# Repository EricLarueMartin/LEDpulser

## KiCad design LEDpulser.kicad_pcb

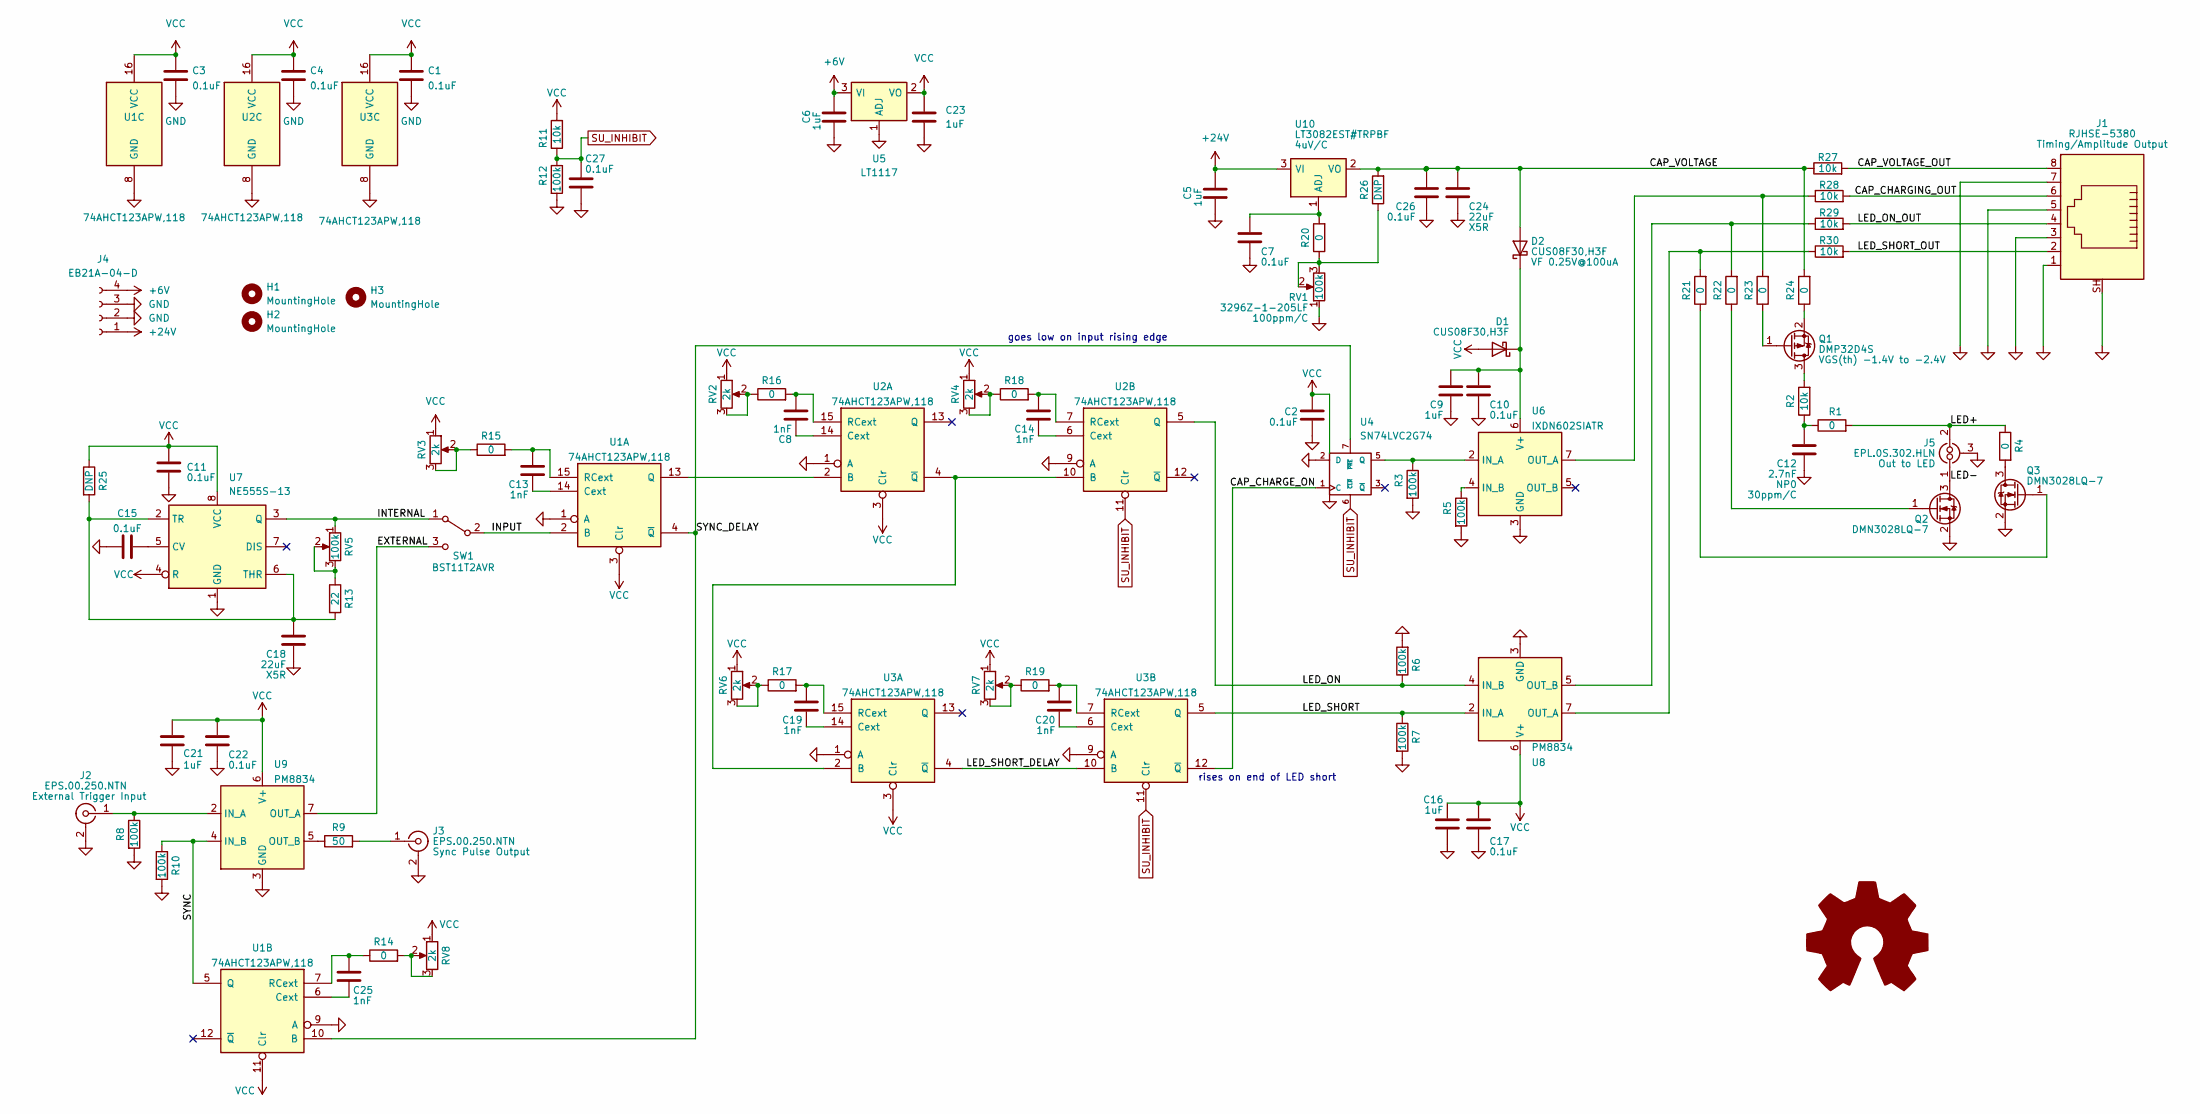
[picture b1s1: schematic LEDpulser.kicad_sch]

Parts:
C1, C2, C3, C4, C10, C11, C15, C17, C22, C26, C27: 0.1uF; C_0603_1608Metric
C5, C6, C9, C16, C21, C23: 1uF; C_0603_1608Metric
C7: 0.1uF; C_0805_2012Metric
C8, C13, C14, C19, C20, C25: 1nF; C_0603_1608Metric
C12: 2.7nF; C_0603_1608Metric
C18, C24: 22uF; C_0805_2012Metric
D1, D2: CUS08F30,H3F; D_SOD-323
H1, H2, H3: MountingHole; MountingHole_3.2mm_M3
J1: RJHSE-5380; RJ45_Amphenol_RJHSE5380
J2, J3: EPS.00.250.NTN; SMA_Amphenol_132203-12_Horizontal
J4: EB21A-04-D; TerminalBlock_Phoenix_MKDS-1,5-4-5.08_1x04_P5.08mm_Horizont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
J5: EPL.0S.302.HLN; FanPinHeader_1x03_P2.54mm_Vertical
Q1: DMP32D4S; SOT-23
Q2, Q3: DMN3028LQ-7; SOT-23
R1, R4, R14, R15, R16, R17, R18, R19, R20, R21, R22, R23, R24: 0; R_0603_1608Metric
R2, R11, R27, R28, R29, R30: 10k; R_0603_1608Metric
R3, R5, R6, R7, R8, R10, R12: 100k; R_0603_1608Metric
R9: 50; R_1206_3216Metric
R13: 22; R_0603_1608Metric
R25, R26: DNP; R_0603_1608Metric
RV1: 100k; Potentiometer_Bourns_3266X_Horizontal; Part# 3296Z-1-205LF
RV2: 2k; Potentiometer_Bourns_3266W_Vertical; Part# 3262X-1-501LF
RV3: 2k; Potentiometer_Bourns_3266X_Horizontal; Part# 3262X-1-501LF
RV4, RV6, RV7: 2k; Potentiometer_Bourns_3266W_Vertical; Part# 3296Y-1-202LF
RV5: 100k; Potentiometer_Bourns_3266X_Horizontal; Part# 3296Z-1-104LF
RV8: 2k; Potentiometer_Bourns_3266X_Horizontal; Part# 3262X-1-202LF
SW1: BST11T2AVR; SW_Lever_1P2T_NKK_GW12LxH
U1, U2, U3: 74AHCT123APW,118; TSSOP-16_4.4x5mm_P0.65mm
U4: SN74LVC2G74; SSOP-8_2.95x2.8mm_P0.65mm
U5: LT1117; SOT-223-3_TabPin2
U6: IXDN602SIATR; SO-8_3.9x4.9mm_P1.27mm
U7: NE555S-13; SO-8_3.9x4.9mm_P1.27mm
U8, U9: PM8834; SO-8_3.9x4.9mm_P1.27mm
U10: LT3082EST#TRPBF; SOT-223-3_TabPin2

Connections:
+6V: C6.1, J4.4, U5.3 (VI)
+24V: C5.1, J4.1, U10.3 (VI)
/CAP_CHARGE_ON: U3.12 (~Q), U4.1 (C)
/CAP_CHARGING_OUT: J1.6, R28.2
/CAP_VOLTAGE: C24.1, C26.1, D2.2 (A), R24.2, R26.2, R27.1, U10.2 (VO)
/CAP_VOLTAGE_OUT: J1.8, R27.2
/EXTERNAL: SW1.3 (C), U9.7 (OUT_A)
/INPUT: SW1.2 (B), U1.2 (B)
/INTERNAL: RV5.1, SW1.1 (A), U7.3 (Q)
/LED+: J5.2 (In2), R1.2, R4.1
/LED-: J5.1 (In1), Q2.3 (D)
/LED_ON: R6.1, U2.5 (Q), U8.4 (IN_B)
/LED_ON_OUT: J1.4, R29.2
/LED_SHORT: R7.1, U3.5 (Q), U8.2 (IN_A)
/LED_SHORT_DELAY: U3.4 (~Q), U3.10 (B)
/LED_SHORT_OUT: J1.2, R30.2
/SYNC: R10.1, U1.5 (Q), U9.4 (IN_B)
/SYNC_DELAY: U1.4 (~Q), U1.10 (B), U4.7 (~PRE)
GND: C1.2, C2.2, C3.2, C4.2, C5.2, C6.2, C7.2, C9.2, C10.2, C11.2, C12.2, C15.2, C16.2, C17.2, C18.2, C21.2, C22.2, C23.2, C24.2, C26.2, C27.2, J1.1, J1.3, J1.5, J1.7, J1.SH, J2.2 (Ext), J3.2 (Ext), J4.2, J4.3, J5.3 (Ext), Q2.2 (S), Q3.2 (S), R3.2, R5.2, R6.2, R7.2, R8.2, R10.2, R12.2, RV1.1, U1.1 (A), U1.8 (GND), U1.9 (A), U2.1 (A), U2.8 (GND), U2.9 (A), U3.1 (A), U3.8 (GND), U3.9 (A), U4.2 (D), U4.4 (GND), U5.1 (ADJ), U6.3 (GND), U7.1 (GND), U8.3 (GND), U9.3 (GND)
unnamed: C7.1, R20.2, U10.1 (ADJ)
unnamed: C8.1, U2.14 (Cext)
unnamed: C8.2, R16.2, U2.15 (RCext)
unnamed: C9.1, C10.1, D1.1 (K), D2.1 (K), U6.6 (V+)
unnamed: C12.1, R1.1, R2.1
unnamed: C13.1, R15.2, U1.15 (RCext)
unnamed: C13.2, U1.14 (Cext)
unnamed: C14.1, R18.2, U2.7 (RCext)
unnamed: C14.2, U2.6 (Cext)
unnamed: C15.1, U7.5 (CV)
unnamed: C18.1, R13.2, R25.2, U7.2 (TR), U7.6 (THR)
unnamed: C19.1, R17.2, U3.15 (RCext)
unnamed: C19.2, U3.14 (Cext)
unnamed: C20.1, R19.2, U3.7 (RCext)
unnamed: C20.2, U3.6 (Cext)
unnamed: C25.1, R14.1, U1.7 (RCext)
unnamed: C25.2, U1.6 (Cext)
unnamed: J2.1 (In), R8.1, U9.2 (IN_A)
unnamed: J3.1 (In), R9.2
unnamed: Q1.1 (G), R23.1
unnamed: Q1.2 (S), R24.1
unnamed: Q1.3 (D), R2.2
unnamed: Q2.1 (G), R22.1
unnamed: Q3.1 (G), R21.1
unnamed: Q3.3 (D), R4.2
unnamed: R3.1, U4.5 (Q), U6.2 (IN_A)
unnamed: R5.1, U6.4 (IN_B)
unnamed: R9.1, U9.5 (OUT_B)
unnamed: R13.1, RV5.2, RV5.3
unnamed: R14.2, RV8.2, RV8.3
unnamed: R15.1, RV3.2, RV3.3
unnamed: R16.1, RV2.2, RV2.3
unnamed: R17.1, RV6.2, RV6.3
unnamed: R18.1, RV4.2, RV4.3
unnamed: R19.1, RV7.2, RV7.3
unnamed: R20.1, R26.1, RV1.2, RV1.3
unnamed: R21.2, R30.1, U8.7 (OUT_A)
unnamed: R22.2, R29.1, U8.5 (OUT_B)
unnamed: R23.2, R28.1, U6.7 (OUT_A)
unnamed: U1.13 (Q), U2.2 (B)
unnamed: U2.4 (~Q), U2.10 (B), U3.2 (B)
SU_INHIBIT: C27.1, R11.1, R12.1, U2.11 (Clr), U3.11 (Clr), U4.6 (~CLR)
VCC: C1.1, C2.1, C3.1, C4.1, C11.1, C16.1, C17.1, C21.1, C22.1, C23.1, D1.2 (A), R11.2, R25.1, RV2.1, RV3.1, RV4.1, RV6.1, RV7.1, RV8.1, U1.3 (Clr), U1.11 (Clr), U1.16 (VCC), U2.3 (Clr), U2.16 (VCC), U3.3 (Clr), U3.16 (VCC), U4.8 (VCC), U5.2 (VO), U7.4 (R), U7.8 (VCC), U8.6 (V+), U9.6 (V+)

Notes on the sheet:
rises on end of LED short
goes low on input rising edge

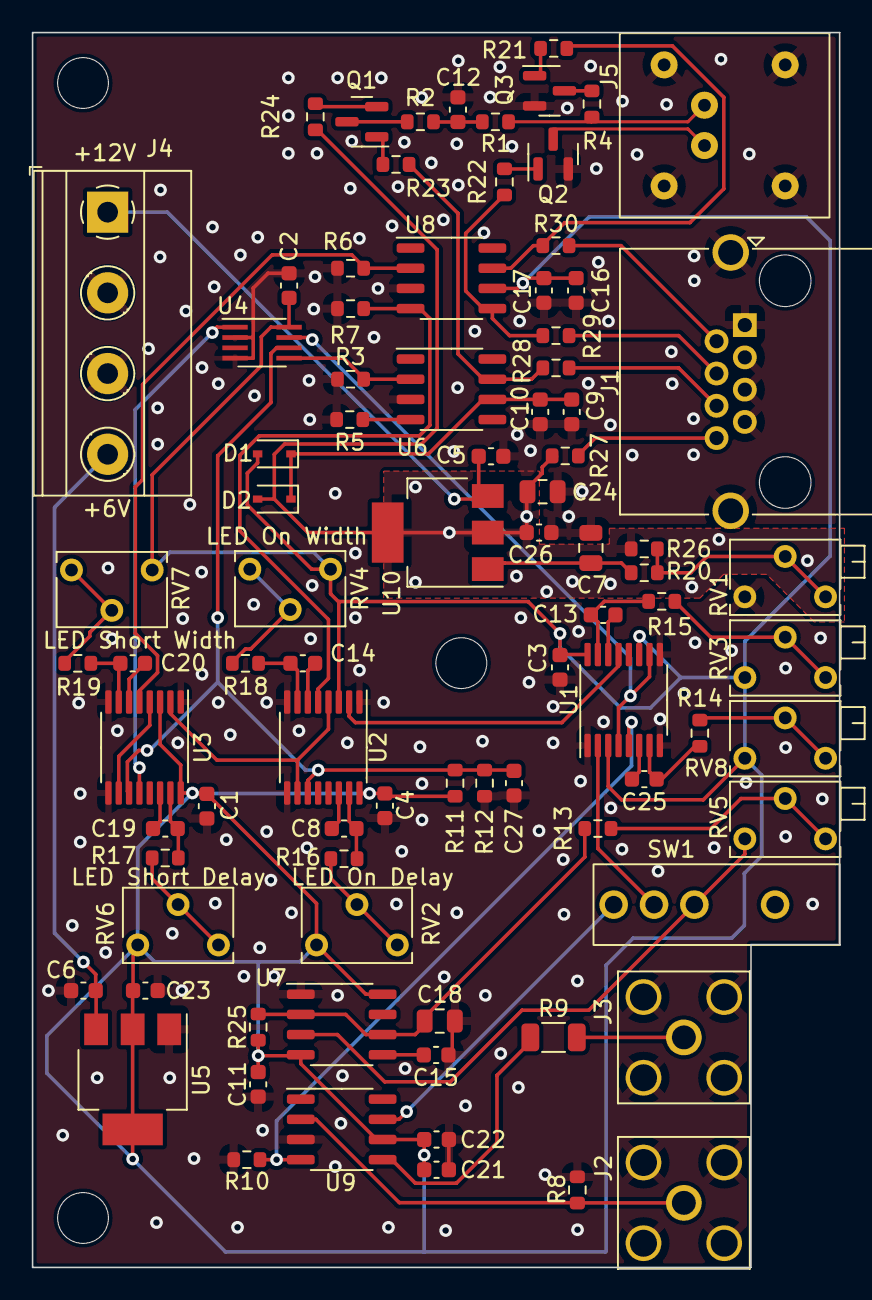
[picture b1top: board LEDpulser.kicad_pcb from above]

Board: 2 copper layers, 50.8 x 77.7 mm, 89 parts (0 on the bottom side), 62 nets.

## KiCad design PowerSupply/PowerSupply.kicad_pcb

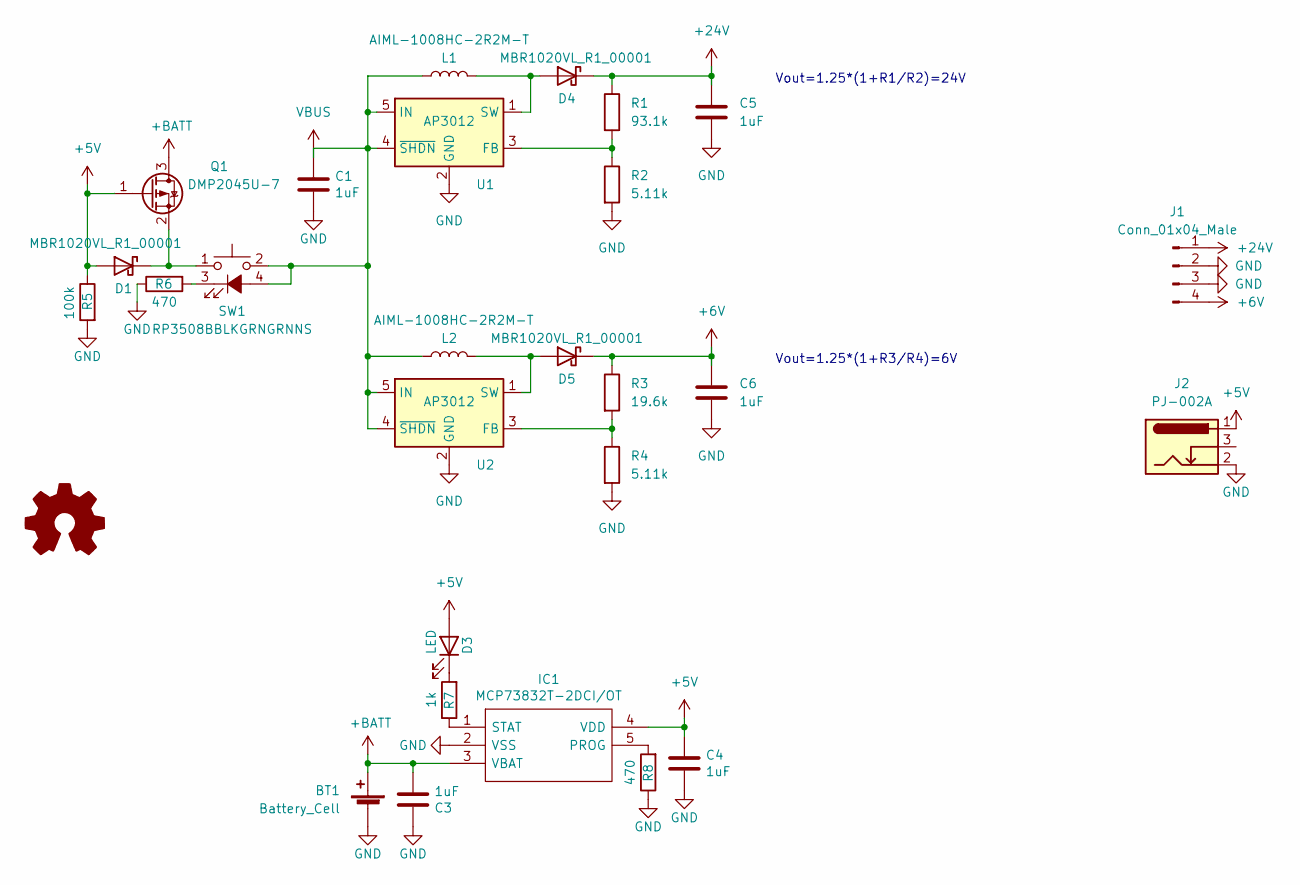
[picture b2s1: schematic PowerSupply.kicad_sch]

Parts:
BT1: Battery_Cell; PinHeader_1x02_P2.54mm_Horizontal
C1, C3, C4, C5, C6: 1uF; C_0603_1608Metric
D1, D4, D5: MBR1020VL_R1_00001; D_SOD-123F
D3: LED; PinHeader_1x02_P2.54mm_Horizontal
IC1: MCP73832T-2DCI/OT; SOT-23-5; Mouser Part Number 579-MCP73832T-2DCIOT
J1: Conn_01x04_Male; EdgePins_4_5mm
J2: PJ-002A; BarrelJack_Horizontal
L1, L2: AIML-1008HC-2R2M-T; L_1008_2520Metric
LOGO1: Logo_Open_Hardware_Small; TUNL LOGO small
Q1: DMP2045U-7; SOT-23
R1: 93.1k; R_0603_1608Metric
R2, R4: 5.11k; R_0603_1608Metric
R3: 19.6k; R_0603_1608Metric
R5: 100k; R_0603_1608Metric
R6, R8: 470; R_0603_1608Metric
R7: 1k; R_0603_1608Metric
SW1: RP3508BBLKGRNGRNNS; RP3508x
U1, U2: AP3012; SOT-23-5

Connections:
+5V: C4.1, D1.2 (A), D3.2 (A), IC1.4 (VDD), J2.1, Q1.1 (G), R5.1
+6V: C6.1, D5.1 (K), J1.4, R3.1
+24V: C5.1, D4.1 (K), J1.1, R1.1
+BATT: BT1.1 (+), C3.2, IC1.3 (VBAT), Q1.3 (D)
GND: BT1.2 (-), C1.2, C3.1, C4.2, C5.2, C6.2, IC1.2 (VSS), J1.2, J1.3, J2.2, R2.2, R4.2, R5.2, R6.1, R8.1, U1.2 (GND), U2.2 (GND)
unnamed: D1.1 (K), Q1.2 (S), SW1.1
unnamed: D3.1 (K), R7.2
unnamed: D4.2 (A), L1.2, U1.1 (SW)
unnamed: D5.2 (A), L2.2, U2.1 (SW)
unnamed: IC1.1 (STAT), R7.1
unnamed: IC1.5 (PROG), R8.2
unnamed: R1.2, R2.1, U1.3 (FB)
unnamed: R3.2, R4.1, U2.3 (FB)
unnamed: R6.2, SW1.3 (K)
VBUS: C1.1, L1.1, L2.1, SW1.2, SW1.4 (A), U1.4 (~SHDN), U1.5 (IN), U2.4 (~SHDN), U2.5 (IN)

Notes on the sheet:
Vout=1.25*(1+R3/R4)=6V
Vout=1.25*(1+R1/R2)=24V

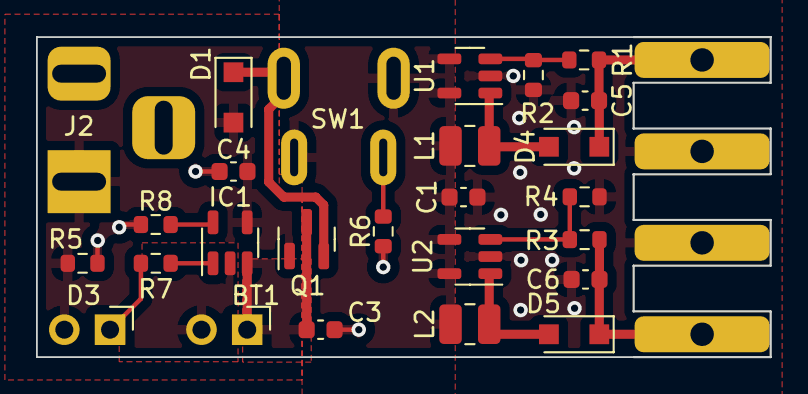
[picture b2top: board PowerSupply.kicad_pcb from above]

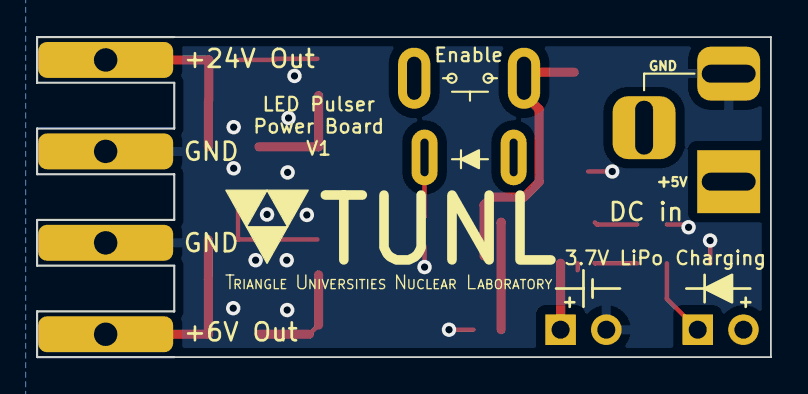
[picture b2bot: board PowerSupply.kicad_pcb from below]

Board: 2 copper layers, 40.8 x 17.8 mm, 28 parts (3 on the bottom side), 15 nets.

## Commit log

2022-02-23 Added LTspice simulation.
2022-02-23 Switched to P-channel charging FET and added LED short path.
2022-02-23 Removed pmosfet from simulation, it was causing issues and was unimportant. Switched GS leads on pmosfet to proper biasing.
2022-02-28 created additional LTspice simulations
    created a few additional LTspice models of the pulser circit LEDpulser3 is the best so far. it seems to be working more or less correctly.
    also created some other files with various circuits as a learning experience
2022-03-01 new push
    push
2022-03-02 Fixed capacitor discharge timing in schematic. Added timing to manual.
2022-03-03 Component selection on most components. Locked package selection.
2022-03-03 Updated models
    primary model is now in LEDPulser4
    added rg58
    added cat8
    tried multiple placements of mosfet
2022-03-03 Component placement and initial hand routing.
2022-03-03 Reducing board length.
2022-03-04 Routed first draft
2022-03-04 Fixed open connection, grounded unused inputs, adjusted connector facing.
2022-03-07 reverting back to last commit
    hopefuly reverting back to last commit pls
2022-03-07 fix
    preseumably fixed some issues where stashed changes were causing problems
2022-03-07 Reverted schematic to previous working version.
2022-03-08 new sim with steps
2022-03-09 Changed switch, added sync pulse monostable, rerouted.
2022-03-10 pushing up to date files
2022-03-10 reverted to previous commit
2022-03-10 Accepted changes correctly this time
    F
2022-03-10 Updated the schematic
    changed the unused monostable. now it is being used as a delay for the output. added a switch to toggle between delay and no delay
2022-03-10 Partial progress. Added resistor of discharge line and started impedance matched traces. Waiting for design decision.
2022-03-10 Added switch STEP file
2022-03-11 Updated Schematic, started placement.
2022-03-11 Modified logic to use flip-flop and reduce front panel adjustments. Changed to +24V for LED capacitor charge supply. Selected components. Rough layout.
2022-03-14 Fixed logic on LED short delay and added startup inhibit to set initial states.
2022-03-15 Routed
2022-04-12 Fixed enable for sync pulse monostable
2022-04-13 Added third mounting hole. Added cutout for LEMO-connector back-side nuts.
2022-04-13 Added labeling to back silk screen
2022-04-21 Added series resistors for pots.
2022-04-29 Added guard ring around 0-20V regulator set pin and output to set current shunt.
2022-05-02 Minor layout edits and generation of fabrication files.
2022-05-16 Added pdf schematic.
2022-08-29 Added optional battery power board.
2022-08-29 Added power switch
2022-08-29 Moved capacitors for regulators to other side of power switch.
2022-08-29 Fixed merge issue.
2022-08-31 Added silk screen and fabrication files.
2022-09-06 Optimized board and changed a few component part numbers based on availability. This version was first production board ordered.
2022-10-14 Fixed issue with shorts on RJ-45 connector shorting out HV regulator.
2023-03-08 Added resistors to prevent shorting power through outputs on RJ45.
